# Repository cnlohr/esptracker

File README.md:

# esptracker
Lighthouse-based tracker using the TS4231

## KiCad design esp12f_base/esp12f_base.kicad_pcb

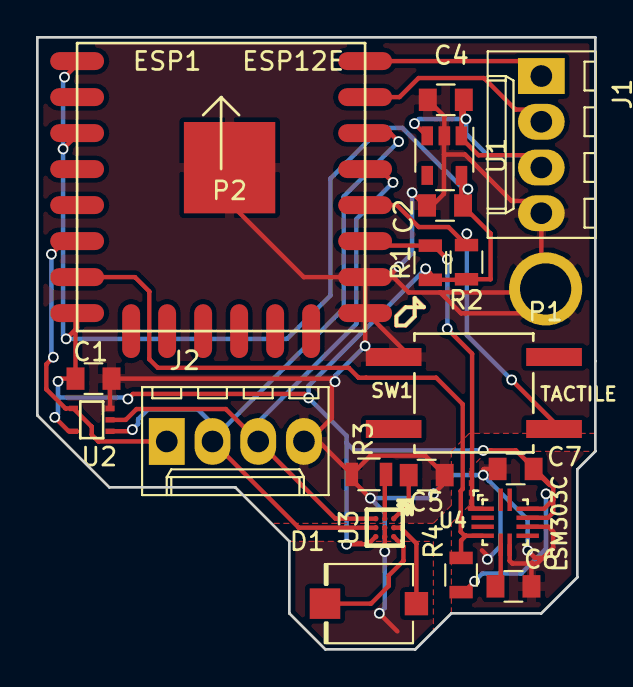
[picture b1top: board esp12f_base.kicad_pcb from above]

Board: 2 copper layers, 31.0 x 34.0 mm, 21 parts (0 on the bottom side), 16 nets.

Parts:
C1, C6, C7: .1u; C_0805
C2: 10u; C_0805
C4, C5: 1u; C_0805
D1: VBPW34FASR
ESP1: ESP12E
J1: PGM; Molex_KK-6410-04_04x2.54mm_Straight
J2: MON; Molex_KK-6410-04_04x2.54mm_Straight
P1, P2: CONN_1; SMTPIN
R1, R2, R4: 4k7; R_0805
R3: 15k; R_0805
SW1: TACTILE; TACTILE10
U1: 3.6V Regulator; SOT-23-5
U2: XOR_SOT_353_74LVC1G86; SOT-353
U3: TS4231
U4: LSM303C; 12LGA

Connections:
+3V3: C1.1, C2.1, C7.1, ESP1.1, ESP1.3, ESP1.8, R1.1, R2.1, R4.2, U1.5, U2.5, U3.C3, U4.9, U4.10
+5V: C4.1, J1.3, U1.1, U1.3
GND: C1.2, C2.2, C4.2, C5.1, C6.2, C7.2, ESP1.15, ESP1.16, J1.4, J2.4, P1.1, P2.1, R3.2, SW1.4, U1.2, U2.3, U3.B2, U3.B3, U4.6, U4.8
I2SI: ESP1.6, J2.1, U2.4
IIN+: D1.2, U3.A2
IIN-: D1.1, U3.A3
unnamed: C5.2, U3.A1
unnamed: C6.1, U4.5
unnamed: ESP1.18, R2.2, SW1.1
unnamed: R3.1, U3.B1
RAWDAT: ESP1.19, J2.3, U2.2, U3.C1
RAWENV: ESP1.20, J2.2, U2.1, U3.C2
RXD: ESP1.21, J1.2
SCL: ESP1.17, R1.2, U4.1
SDA: ESP1.7, R4.1, U4.4
TXD: ESP1.22, J1.1

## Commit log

2018-04-11 Add ESP12F base
2018-04-21 Update gen2
2018-04-21 add custom command option
2018-04-22 Bump versions - try to track.
2018-04-25 Make work.
2018-04-25 bump to fix misalignment
2018-04-25 bump submodule
2018-04-26 Add some processing tools
2018-04-26 Update with fully functional grabber.
2018-07-21 Add data stream.
2018-07-21 Update chatlog
2018-07-22 Update chat log
2018-08-05 bump gen2 process
2018-08-05 bump more analysis tools
2018-08-05 add decoding chatlog

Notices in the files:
esp12f_base/esp12f_base.kicad_pcb:
(C) 2018 C. Lohr
